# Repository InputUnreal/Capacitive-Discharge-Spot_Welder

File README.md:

# Capacitive-Discharge-Spot_Welder
18650 Capacitive Discharge Spot Welder

Cyclinderical Lithium Ion Spot Welder designed to be as cost effecitive as possible. Uses capacitors instead of battery, to reduce the pulse deration (dump less heat into the battery)

96 * Capacitors are 16V 10000UF (ebay or aliexpress around 40 USD for 100 PCS)
8 * IPLU300N04S4-R8 MOSFET (ebay or aliexpress 5 USD for 10 PCS)
2 * TC4422 9A gate drivers (ebay or aliexpress 3 USD for 5 PCS)
PCB -> 8 USD from JLCPCB

Requires external trigger source from MCU (PUSH PULL) 

Capacitors are to be solder about 10mm from PCB so extra solder can be added also 
bend the legs rather then trimming them

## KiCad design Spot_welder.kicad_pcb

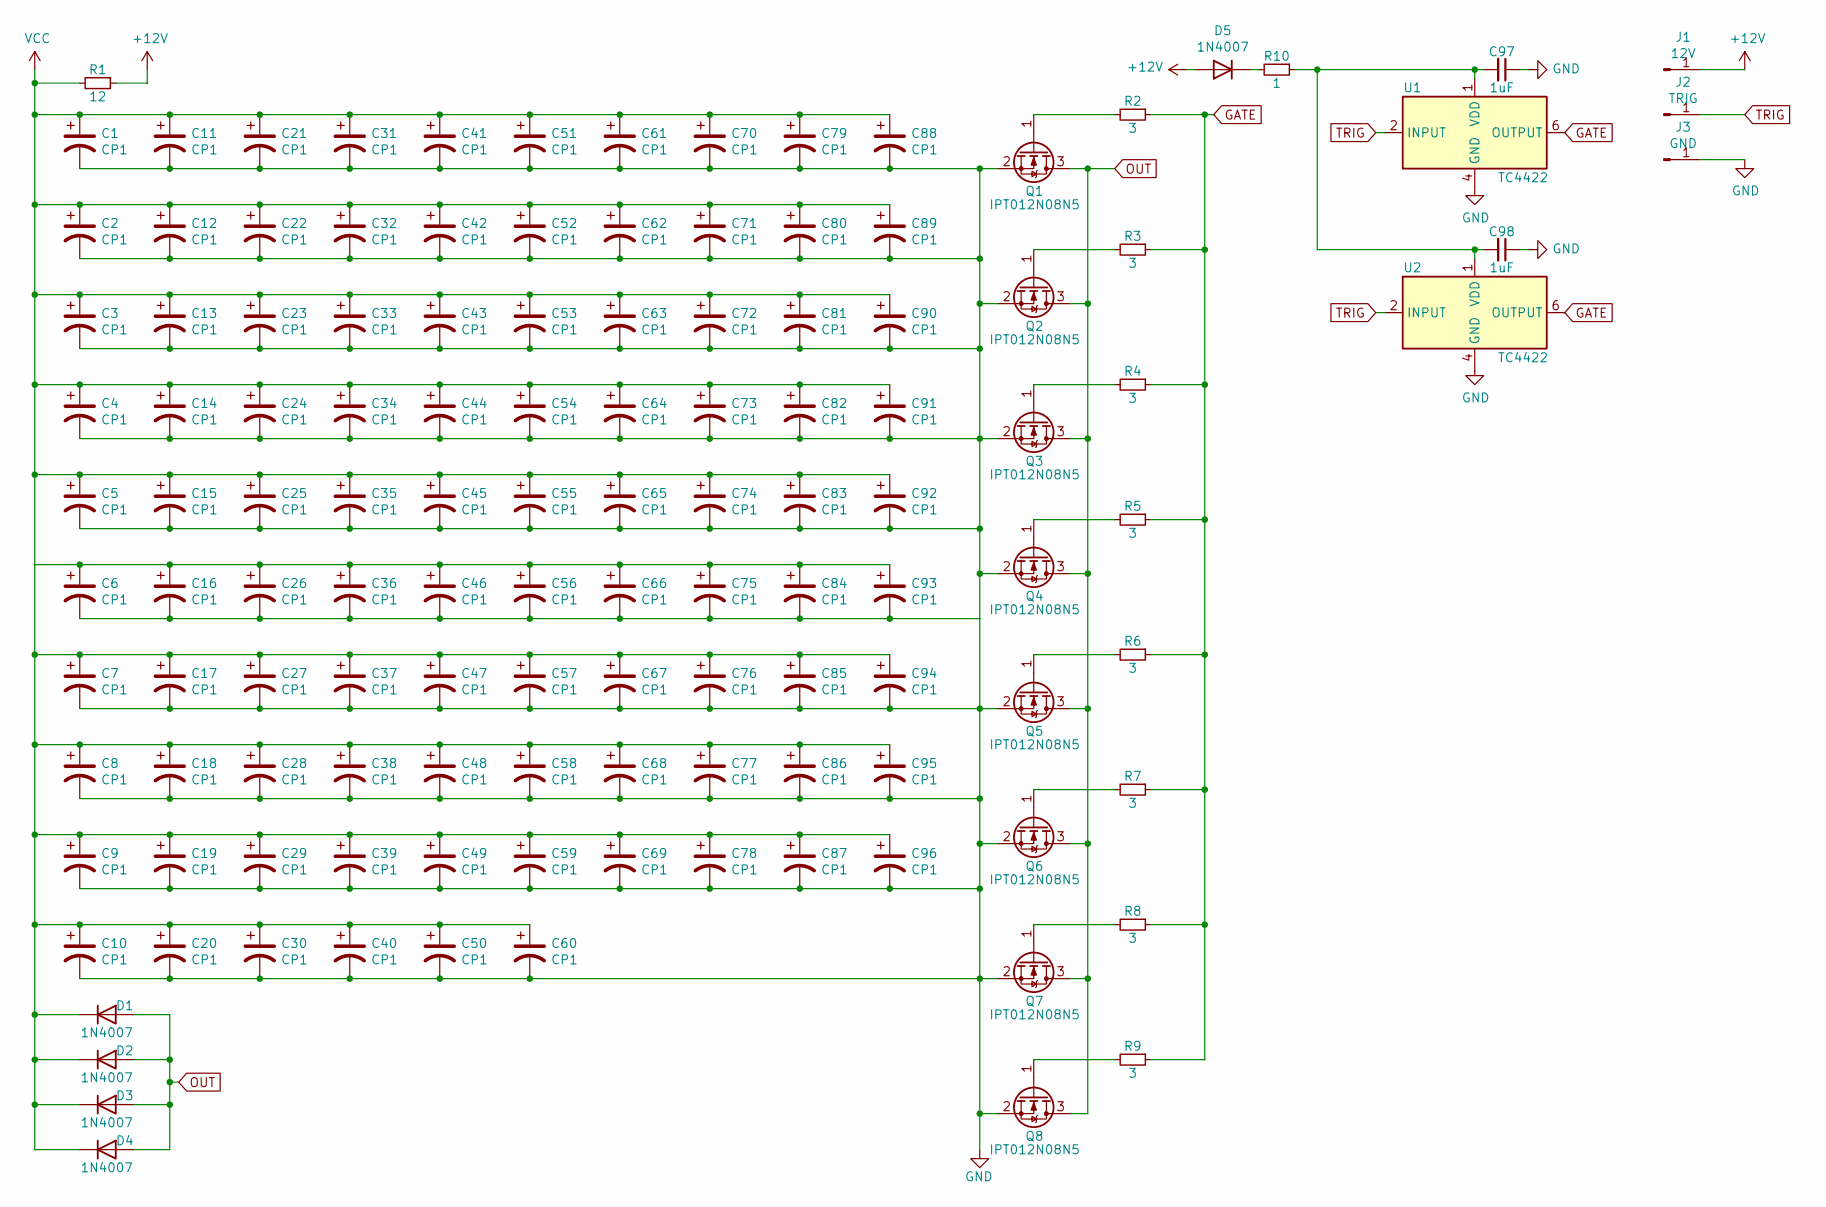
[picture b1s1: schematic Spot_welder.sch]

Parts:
C1, C2, C3, C4, C5, C6, C7, C8, C9, C10, C11, C12, C13, C14, C15, C16, C17, C18, C19, C20, C21, C22, C23, C24, C25, C26, C27, C28, C29, C30, C31, C32, C33, C34, C35, C36, C37, C38, C39, C40, C41, C42, C43, C44, C45, C46, C47, C48, C49, C50, C51, C52, C53, C54, C55, C56, C57, C58, C59, C60, C61, C62, C63, C64, C65, C66, C67, C68, C69, C70, C71, C72, C73, C74, C75, C76, C77, C78, C79, C80, C81, C82, C83, C84, C85, C86, C87, C88, C89, C90, C91, C92, C93, C94, C95, C96: CP1; CP_Radial_D16.0mm_P7.50mm
C97, C98: 1uF; C_0805_2012Metric
D1, D2, D3, D4, D5: 1N4007; D_SMA
J1: 12V; SolderWire-0.5sqmm_1x01_D0.9mm_OD2.1mm
J2: TRIG; SolderWire-0.127sqmm_1x01_D0.48mm_OD1mm
J3: GND; SolderWire-0.5sqmm_1x01_D0.9mm_OD2.1mm
Q1, Q2, Q3, Q4, Q5, Q6, Q7, Q8: IPT012N08N5; Infineon_PG-HSOF-8-1
R1: 12; R_Axial_DIN0207_L6.3mm_D2.5mm_P7.62mm_Horizontal
R2, R3, R4, R5, R6, R7, R8, R9: 3; R_0805_2012Metric
R10: 1; R_0805_2012Metric
U1, U2: TC4422; SOIC-8_3.9x4.9mm_P1.27mm

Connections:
+12V: D5.2 (A), J1.1, R1.1
GATE: R2.1, R3.1, R4.1, R5.1, R6.1, R7.1, R8.1, R9.1, U1.6 (OUTPUT), U1.7 (OUTPUT), U2.6 (OUTPUT), U2.7 (OUTPUT)
GND: C1.2, C2.2, C3.2, C4.2, C5.2, C6.2, C7.2, C8.2, C9.2, C10.2, C11.2, C12.2, C13.2, C14.2, C15.2, C16.2, C17.2, C18.2, C19.2, C20.2, C21.2, C22.2, C23.2, C24.2, C25.2, C26.2, C27.2, C28.2, C29.2, C30.2, C31.2, C32.2, C33.2, C34.2, C35.2, C36.2, C37.2, C38.2, C39.2, C40.2, C41.2, C42.2, C43.2, C44.2, C45.2, C46.2, C47.2, C48.2, C49.2, C50.2, C51.2, C52.2, C53.2, C54.2, C55.2, C56.2, C57.2, C58.2, C59.2, C60.2, C61.2, C62.2, C63.2, C64.2, C65.2, C66.2, C67.2, C68.2, C69.2, C70.2, C71.2, C72.2, C73.2, C74.2, C75.2, C76.2, C77.2, C78.2, C79.2, C80.2, C81.2, C82.2, C83.2, C84.2, C85.2, C86.2, C87.2, C88.2, C89.2, C90.2, C91.2, C92.2, C93.2, C94.2, C95.2, C96.2, C97.1, C98.1, J3.1, Q1.2 (S), Q2.2 (S), Q3.2 (S), Q4.2 (S), Q5.2 (S), Q6.2 (S), Q7.2 (S), Q8.2 (S), U1.4 (GND), U1.5 (GND), U2.4 (GND), U2.5 (GND)
unnamed: C97.2, C98.2, R10.1, U1.1 (VDD), U1.8 (VDD), U2.1 (VDD), U2.8 (VDD)
unnamed: D5.1 (K), R10.2
unnamed: Q1.1 (G), R2.2
unnamed: Q2.1 (G), R3.2
unnamed: Q3.1 (G), R4.2
unnamed: Q4.1 (G), R5.2
unnamed: Q5.1 (G), R6.2
unnamed: Q6.1 (G), R7.2
unnamed: Q7.1 (G), R8.2
unnamed: Q8.1 (G), R9.2
OUT: D1.2 (A), D2.2 (A), D3.2 (A), D4.2 (A), Q1.3 (D), Q2.3 (D), Q3.3 (D), Q4.3 (D), Q5.3 (D), Q6.3 (D), Q7.3 (D), Q8.3 (D)
TRIG: J2.1, U1.2 (INPUT), U2.2 (INPUT)
VCC: C1.1, C2.1, C3.1, C4.1, C5.1, C6.1, C7.1, C8.1, C9.1, C10.1, C11.1, C12.1, C13.1, C14.1, C15.1, C16.1, C17.1, C18.1, C19.1, C20.1, C21.1, C22.1, C23.1, C24.1, C25.1, C26.1, C27.1, C28.1, C29.1, C30.1, C31.1, C32.1, C33.1, C34.1, C35.1, C36.1, C37.1, C38.1, C39.1, C40.1, C41.1, C42.1, C43.1, C44.1, C45.1, C46.1, C47.1, C48.1, C49.1, C50.1, C51.1, C52.1, C53.1, C54.1, C55.1, C56.1, C57.1, C58.1, C59.1, C60.1, C61.1, C62.1, C63.1, C64.1, C65.1, C66.1, C67.1, C68.1, C69.1, C70.1, C71.1, C72.1, C73.1, C74.1, C75.1, C76.1, C77.1, C78.1, C79.1, C80.1, C81.1, C82.1, C83.1, C84.1, C85.1, C86.1, C87.1, C88.1, C89.1, C90.1, C91.1, C92.1, C93.1, C94.1, C95.1, C96.1, D1.1 (K), D2.1 (K), D3.1 (K), D4.1 (K), R1.2

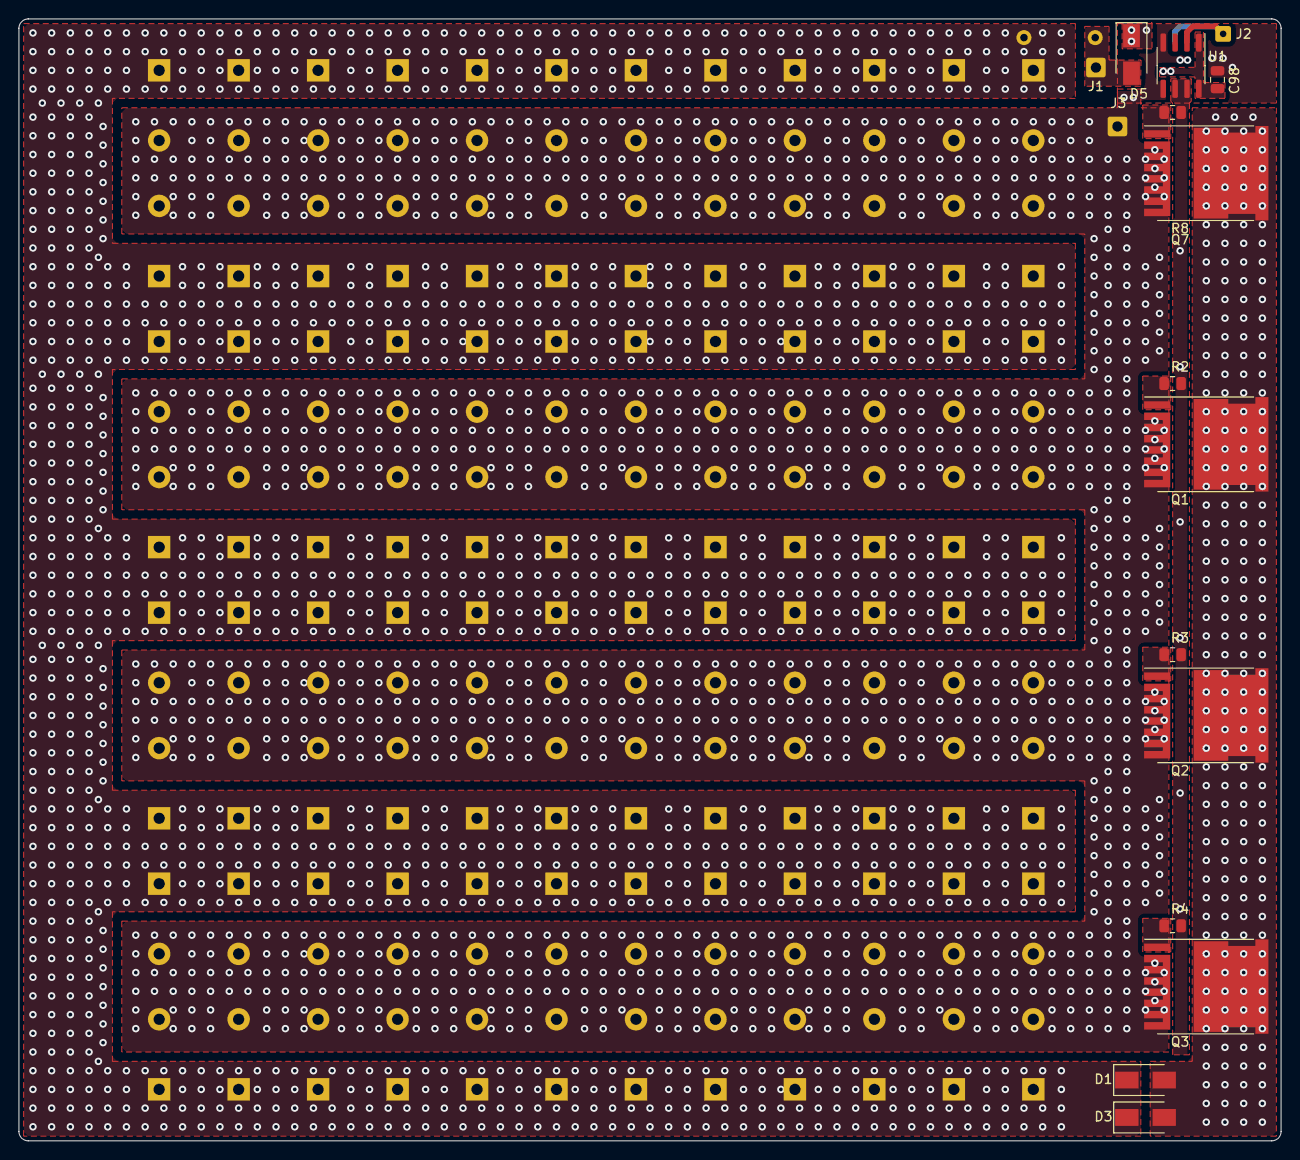
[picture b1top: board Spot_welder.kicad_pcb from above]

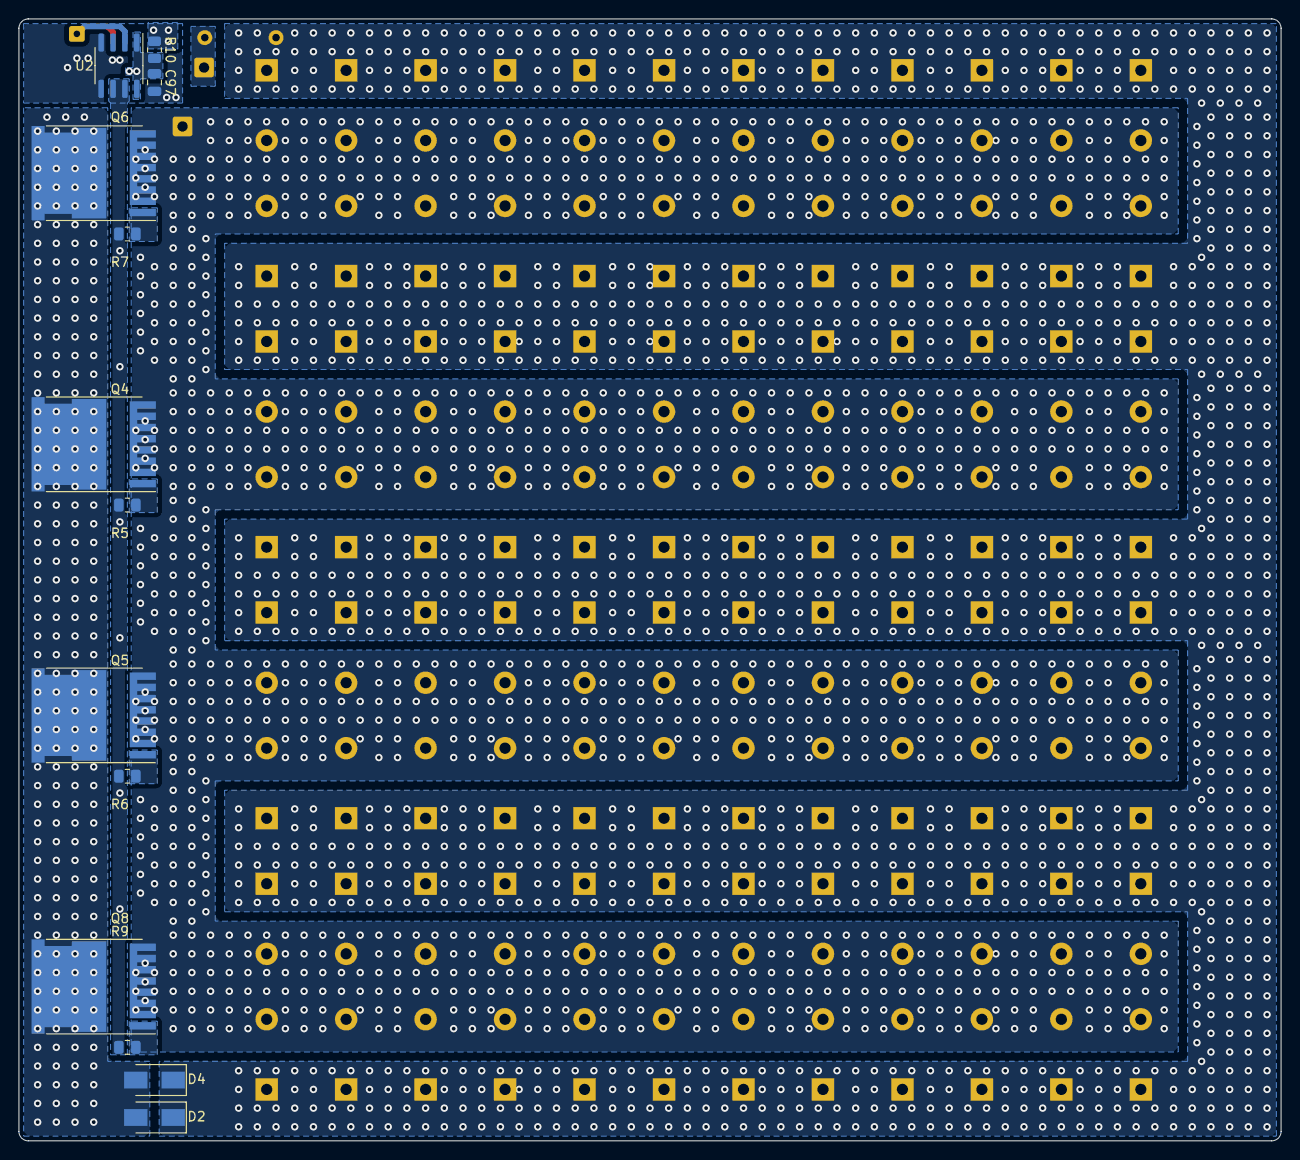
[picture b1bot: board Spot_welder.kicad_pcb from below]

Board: 2 copper layers, 135.0 x 120.0 mm, 126 parts (61 on the bottom side), 16 nets.
